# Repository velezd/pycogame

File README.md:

# pycoGame

pycoGame is a handheld game console based on Raspberry Pi Pico and a MicroPython library for easy game development inspired by pygame.

More information at http://zveleba.cz/pages/blog/posts/pycogame.html

## Content
- Open hardware game console
- MicroPython library pycogame
- Game launcher
- Example games
    - FlappyTux (Flappy Bird clone)
    - Micronoid (Arkanoid clone)
    - MicroMaze 3D (Raycaster maze game)
- Game development tools
    - precompile
    - img2rgb565

## Download

Version 1.0

## Installation

- Program firmware onto RPi Pico
    ./micropython/ports/rp2/build-PICO/firmware.uf2
- Copy game launcher files to RPi Pico flash.
  Easiest tool for that is Thonny IDE, also useful for debugging.
- Copy games to SD Card

## Build firmware

- Get submodules and build container

    `make setup`

- Build

    `make build`

- Cleanup (optional)

    `make cleanup`

## Pre-compile MicroPython scripts

MicroPython scripts can be pre-compiled for 
faster execution and reduced memory usage.

This will run the build container and execute `make setup` if needed.

`./precompile.sh games/Test/game.py`

## Convering images to RGB565 format

Requires python libraries `scikit-image` and `PIL` (on fedora: `sudo dnf install python3-scikit-image python3-pillow`).
Multiple images can be converted at once.
The script contains workaround for inaccurate colors on the LCD (gamma correction).

Convered images are stored in directory `converted` 
and gamma corrected images are kept in directory
`gamma_corrected`, so you can use them to sample the
final color value.

`./img2rgb565.py img1.png img2.png ...`

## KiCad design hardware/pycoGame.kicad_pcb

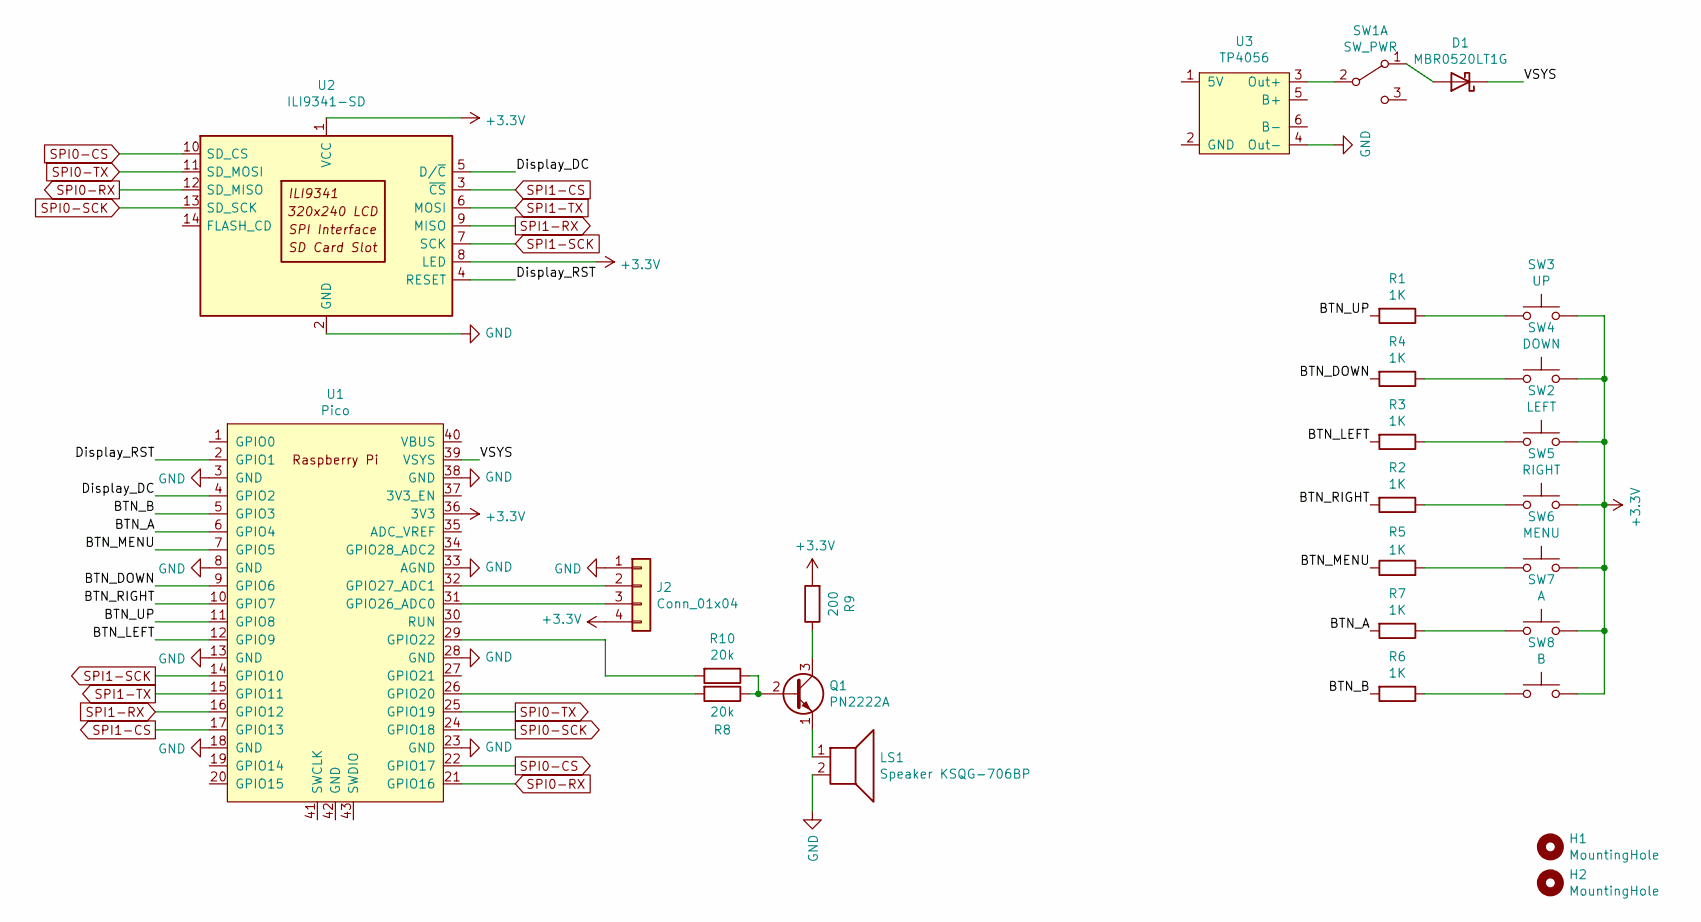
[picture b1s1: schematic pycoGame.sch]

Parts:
D1: MBR0520LT1G; D_SOD-123
H1, H2: MountingHole; MountingHole_3.2mm_M3_ISO14580_Pad
J2: Conn_01x04; PinHeader_1x04_P2.54mm_Vertical
LS1: Speaker KSQG-706BP; Speaker_KSQG-706BP
Q1: PN2222A; TO-92_Inline
R1, R2, R3, R4, R5, R6, R7: 1K; R_Axial_DIN0207_L6.3mm_D2.5mm_P7.62mm_Horizontal
R8, R10: 20k; R_Axial_DIN0207_L6.3mm_D2.5mm_P7.62mm_Horizontal
R9: 200; R_Axial_DIN0207_L6.3mm_D2.5mm_P7.62mm_Horizontal
SW1: SW_PWR; switch
SW2: LEFT; SW_PUSH_6mm_H5mm
SW3: UP; SW_PUSH_6mm_H5mm
SW4: DOWN; SW_PUSH_6mm_H5mm
SW5: RIGHT; SW_PUSH_6mm_H5mm
SW6: MENU; SW_PUSH_6mm_H5mm
SW7: A; SW_PUSH_6mm_H5mm
SW8: B; SW_PUSH_6mm_H5mm
U1: Pico; RPi_Pico_SMD_TH
U2: ILI9341-SD
U3: TP4056

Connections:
+3V3: J2.4, R9.2, SW2.1, SW3.2, SW4.2, SW5.1, SW6.2, SW7.2, SW8.2, U1.36 (3V3), U2.1 (VCC), U2.8 (LED)
/BTN_A: R7.2, U1.6 (GPIO4)
/BTN_B: R6.2, U1.5 (GPIO3)
/BTN_DOWN: R4.2, U1.9 (GPIO6)
/BTN_LEFT: R3.2, U1.12 (GPIO9)
/BTN_MENU: R5.1, U1.7 (GPIO5)
/BTN_RIGHT: R2.2, U1.10 (GPIO7)
/BTN_UP: R1.2, U1.11 (GPIO8)
/Display_DC: U1.4 (GPIO2), U2.5 (D/~C)
/Display_RST: U1.2 (GPIO1), U2.4 (RESET)
/VSYS: D1.1 (K), U1.39 (VSYS)
GND: J2.1, LS1.2, U1.3 (GND), U1.8 (GND), U1.13 (GND), U1.18 (GND), U1.23 (GND), U1.28 (GND), U1.33 (AGND), U1.38 (GND), U2.2 (GND), U3.4 (Out-)
unnamed: D1.2 (A), SW1.1 (A)
unnamed: J2.2, U1.32 (GPIO27_ADC1)
unnamed: J2.3, U1.31 (GPIO26_ADC0)
unnamed: LS1.1, Q1.1 (E)
unnamed: Q1.2 (B), R8.1, R10.1
unnamed: Q1.3 (C), R9.1
unnamed: R1.1, SW3.1
unnamed: R2.1, SW5.2
unnamed: R3.1, SW2.2
unnamed: R4.1, SW4.1
unnamed: R5.2, SW6.1
unnamed: R6.1, SW8.1
unnamed: R7.1, SW7.1
unnamed: R8.2, U1.26 (GPIO20)
unnamed: R10.2, U1.29 (GPIO22)
unnamed: SW1.2 (B), U3.3 (Out+)
SPI0-CS: U1.22 (GPIO17), U2.10 (SD_CS)
SPI0-RX: U1.21 (GPIO16), U2.12 (SD_MISO)
SPI0-SCK: U1.24 (GPIO18), U2.13 (SD_SCK)
SPI0-TX: U1.25 (GPIO19), U2.11 (SD_MOSI)
SPI1-CS: U1.17 (GPIO13), U2.3 (~CS)
SPI1-RX: U1.16 (GPIO12), U2.9 (MISO)
SPI1-SCK: U1.14 (GPIO10), U2.7 (SCK)
SPI1-TX: U1.15 (GPIO11), U2.6 (MOSI)

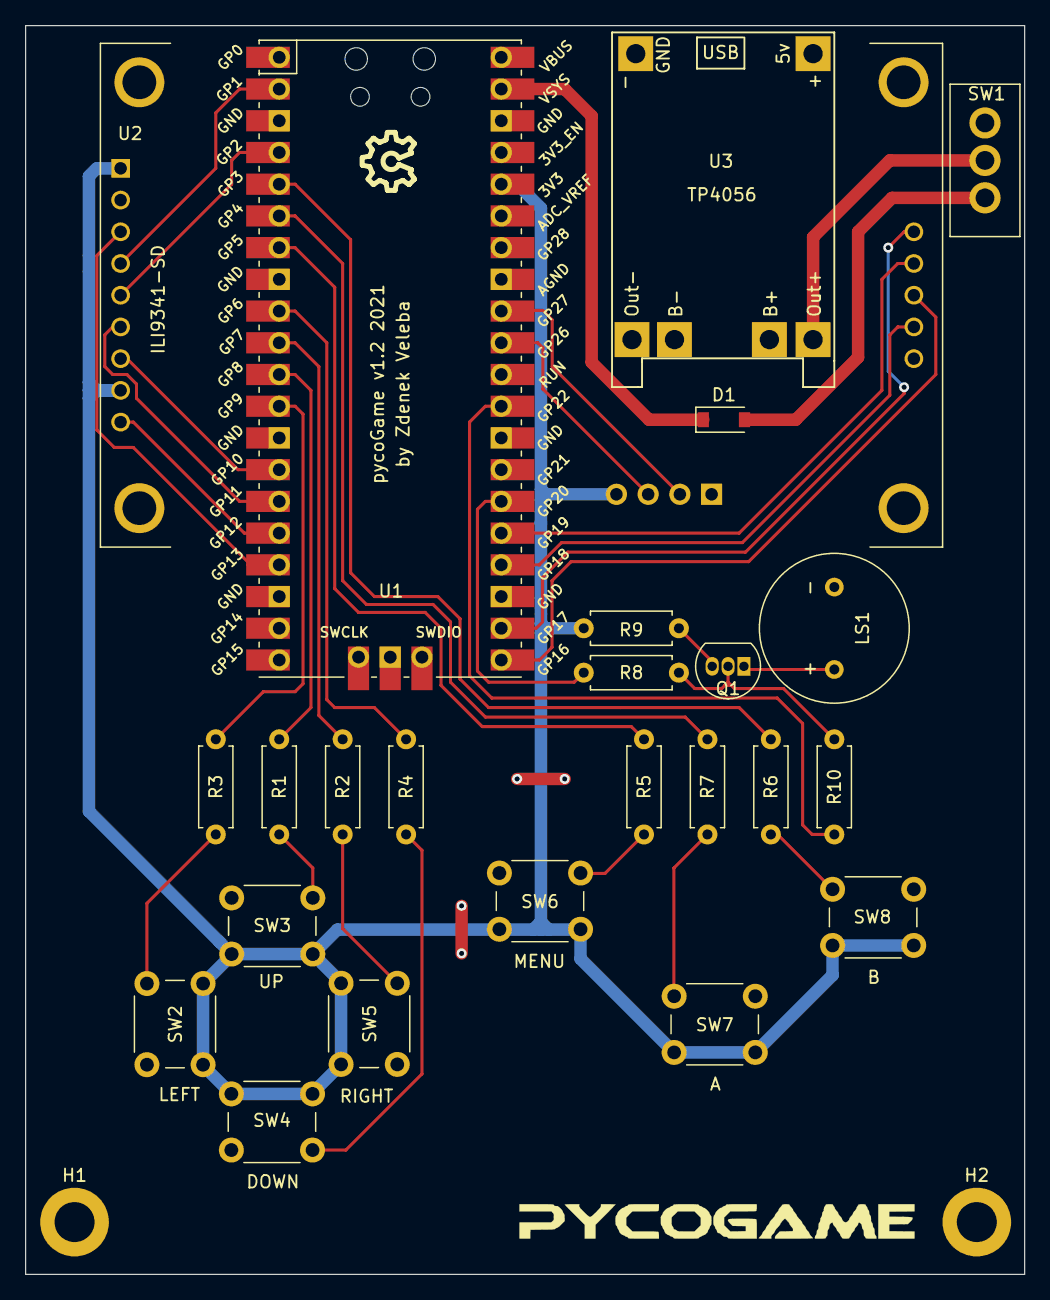
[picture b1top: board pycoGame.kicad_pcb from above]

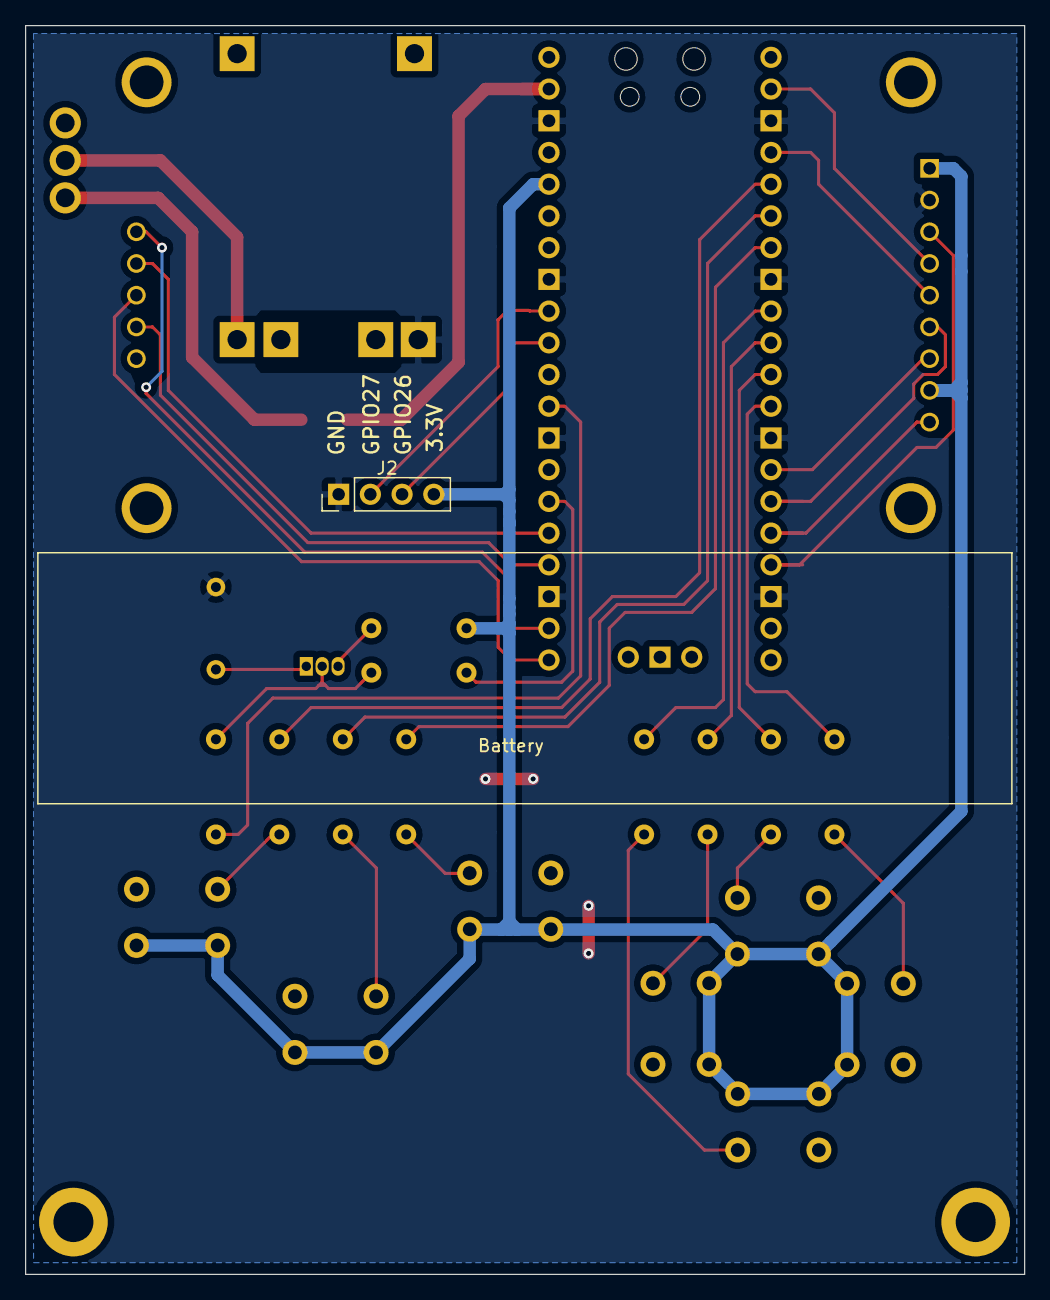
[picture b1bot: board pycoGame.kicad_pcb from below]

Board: 2 copper layers, 80.0 x 100.0 mm, 28 parts (2 on the bottom side), 36 nets.

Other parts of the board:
Battery: BatteryHolder 18650 no pads; BatteryHolder-18650-no-pads

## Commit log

2021-06-05 Add micropython submodule
2023-06-01 First release
2023-06-15 Add new levels to Micronoid
2023-06-15 Change ball speed based on difficulty in Micronoid
